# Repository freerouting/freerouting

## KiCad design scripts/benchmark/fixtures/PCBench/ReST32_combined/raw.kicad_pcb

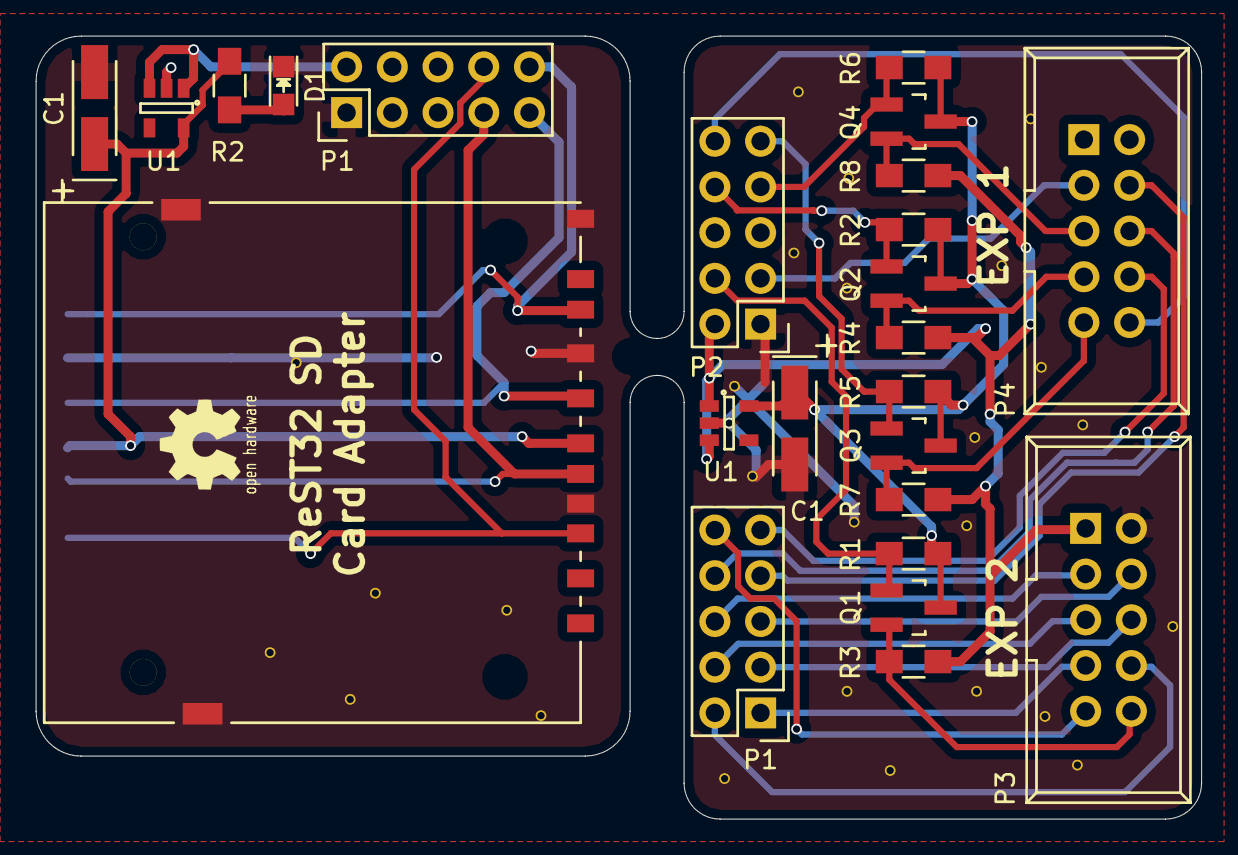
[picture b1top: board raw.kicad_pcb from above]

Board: 2 copper layers, 64.8 x 43.5 mm, 24 parts (0 on the bottom side), 28 nets.

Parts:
C1: 2.2uF; TantalC_SizeA_EIA-3216_HandSoldering
C1#2: CP1_Small; TantalC_SizeA_EIA-3216_HandSoldering
CON1: uSD_Card; SD_Card_Receptacle
D1: Led_Small; LED_0805
P1, P1#2, P2: CONN_02X05; Pin_Header_Straight_2x05
P3, P4: CONN_02X05; IDC_Header_Straight_10pins
Q1, Q2, Q3, Q4: BSS138; SOT-23_Handsoldering
R1, R2, R3, R4, R5, R6, R7, R8: 10K; R_0805_HandSoldering
R2#2: 1K; R_0805_HandSoldering
U1, U1#2: MIC5205; SOT-23-5

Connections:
+3V3: C1.1, C1#2.1, CON1.4, Q1.3, Q2.3, Q3.3, Q4.3, R1.1, R2.1, R2#2.1, R5.1, R6.1, U1.5, U1#2.5
+5V: P1#2.2, P2.2, P3.1, R3.1, R4.1, R7.1, R8.1, U1.1, U1.3, U1#2.1, U1#2.3
/BEEP: P3.10, Q1.2, R3.2
/CS: P4.7, Q2.2, R4.2
/DISPLAY_CD: P1.2, P3.8
/DISPLAY_CS: P1.1, P3.7
/DISPLAY_D0: P1.4, P3.5
/DISPLAY_D1: P1.3, P3.6
/DISPLAY_D2: P1.6, P3.3
/DISPLAY_D3: P1.5, P3.4
/DISPLAY_D4: P1.8, P4.6
/DISPLAY_D5: P1.7, P4.4
/DISPLAY_D6: P1.10, P3.9
/DISPLAY_D7: P1.9, P4.8
/DISPLAY_RD: P2.3, P4.3
/DISPLAY_WR: P2.4, Q1.1, R1.2
/MISO: P2.10, P4.10
/MOSI: P4.5, Q4.2, R8.2
/SCK: P4.9, Q3.2, R7.2
/SPI-CS: CON1.2, P1#2.8
/SPI-MISO: CON1.7, P1#2.10
/SPI-MOSI: CON1.3, P1#2.7
/SPI-SCK: CON1.5, P1#2.9
/SPI_CS1: P2.8, Q2.1, R2.2
/SPI_MOSI: P2.7, Q4.1, R6.2
/SPI_SCK: P2.9, Q3.1, R5.2
GND: C1.2, C1#2.2, CON1.6, CON1.10, CON1.11, CON1.12, CON1.13, D1.1, P1#2.1, P2.1, P3.2, U1.2, U1#2.2
unnamed: D1.2, R2#2.2

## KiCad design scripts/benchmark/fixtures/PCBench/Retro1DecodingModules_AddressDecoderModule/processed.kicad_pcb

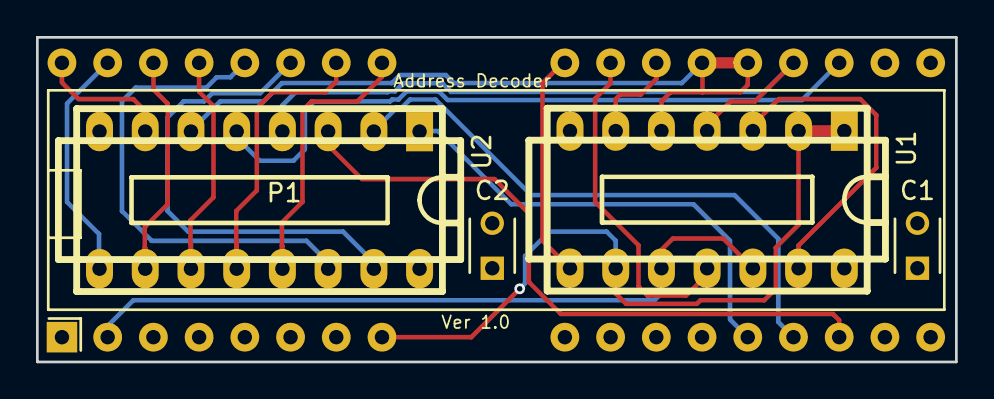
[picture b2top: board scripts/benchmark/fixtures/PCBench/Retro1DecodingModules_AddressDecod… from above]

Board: 4 copper layers, 51.1 x 18.0 mm, 5 parts (0 on the bottom side), 22 nets.

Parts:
C1, C2: .1uf; C_Disc_D3_P2.5
P1: CONN_02X20_DIP40; decoder_footprint
U1: 74LS00; dil_14-300_socket
U2: 74LS138N; dil_16-300_socket

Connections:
A8: P1.16, U2.1
A9: P1.17, U2.2
A10: P1.18, U2.3
A13: P1.23, U2.5
A14: P1.24, U1.4, U2.4
A15: P1.25, P1.26, U1.5, U2.6
CS7: P1.39, U2.9
CS8: P1.40, U2.7
CS_ACIA1: P1.33, U2.13
CS_ACIA2: P1.34, U2.12
CS_RTC: P1.38, U2.10
CS_SID: P1.37, U2.11
CS_VIA1: P1.35, U2.15
CS_VIA2: P1.36, U2.14
GND: C1.1, C2.2, P1.20, U1.7, U2.8
unnamed: U1.3, U1.13
OE: P1.29, U1.8
PHI2: P1.2, U1.10, U1.12
ROM_CE: P1.27, U1.6
RW: P1.8, U1.1, U1.2, U1.9
VCC: C1.2, C2.1, P1.1, P1.21, U1.14, U2.16
WE: P1.28, U1.11

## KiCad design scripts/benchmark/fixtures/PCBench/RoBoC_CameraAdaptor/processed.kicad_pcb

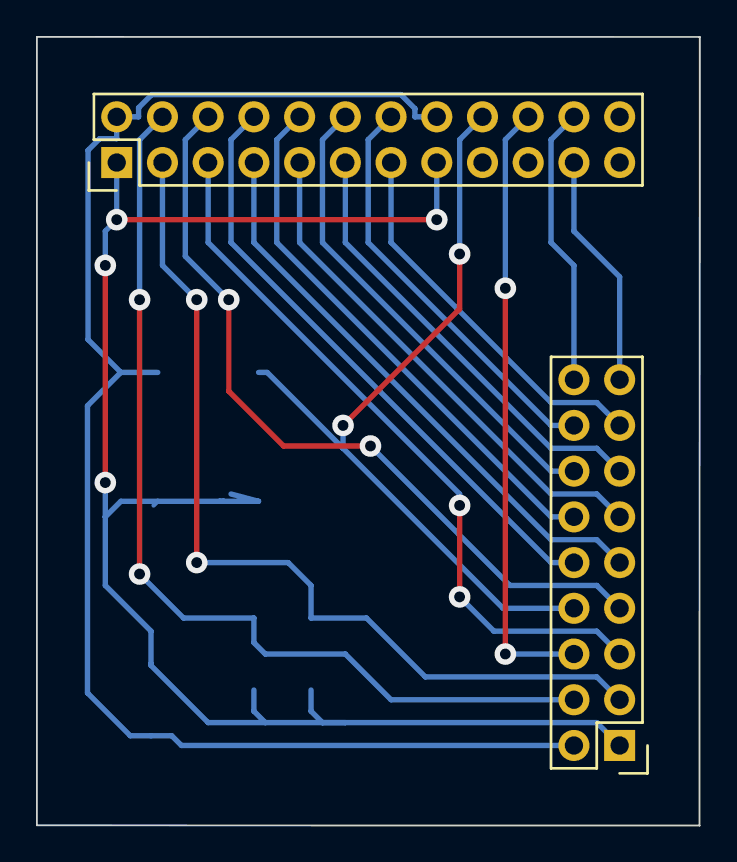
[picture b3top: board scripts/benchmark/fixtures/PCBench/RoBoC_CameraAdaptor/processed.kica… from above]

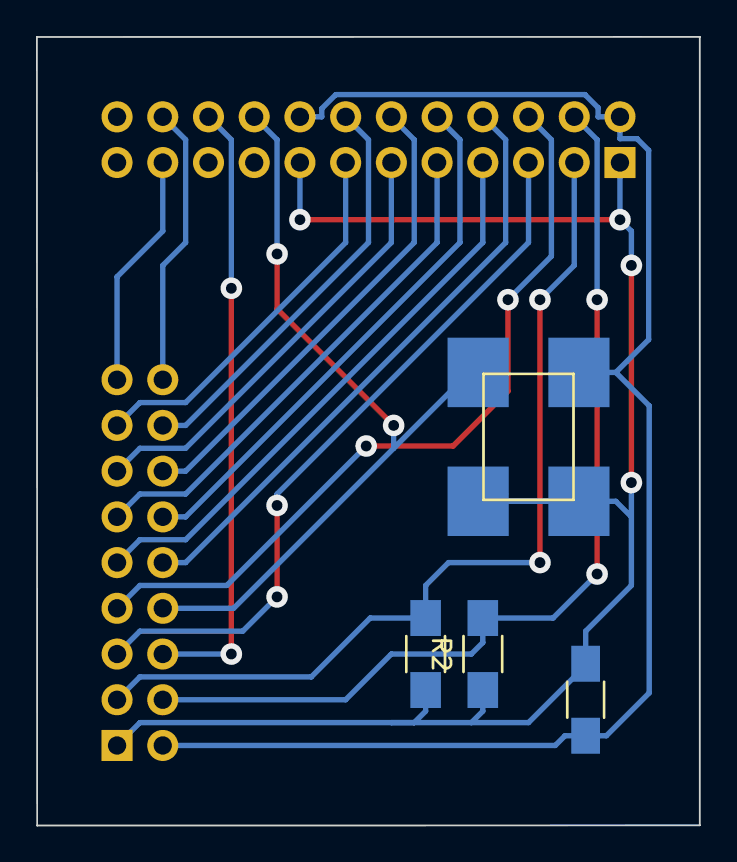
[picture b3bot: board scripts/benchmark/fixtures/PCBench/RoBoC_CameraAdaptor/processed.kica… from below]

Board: 2 copper layers, 36.8 x 43.8 mm, 6 parts (4 on the bottom side), 18 nets.

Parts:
C1: 1uF; C_1206_HandSoldering
P1: CONN_02X12; Pin_Header_Straight_2x12
P2: CONN_02X09; Pin_Header_Straight_2x09
R1, R2: 4.7k; R_1206_HandSoldering
U1: Oscillator; oscillator

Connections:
+3V3: C1.1, P1.1, P1.15, P2.1, R1.1, R2.1, U1.1, U1.4
/D0: P1.14, P2.16
/D1: P1.13, P2.15
/D2: P1.12, P2.14
/D3: P1.11, P2.13
/D4: P1.10, P2.12
/D5: P1.9, P2.11
/D6: P1.8, P2.10
/D7: P1.7, P2.9
/Href: P1.20, P2.6
/PCLK: P1.6, P2.7
/PWDN: P1.22, P2.18
/RESET: P1.21, P2.17
/SIOC: P1.3, P2.3, R1.2
/SIOD: P1.4, P2.4, R2.2
/VSync: P1.5, P2.5
/XCLK: P1.18, P2.8, U1.3
GND: C1.2, P1.2, P1.16, P2.2, U1.2
